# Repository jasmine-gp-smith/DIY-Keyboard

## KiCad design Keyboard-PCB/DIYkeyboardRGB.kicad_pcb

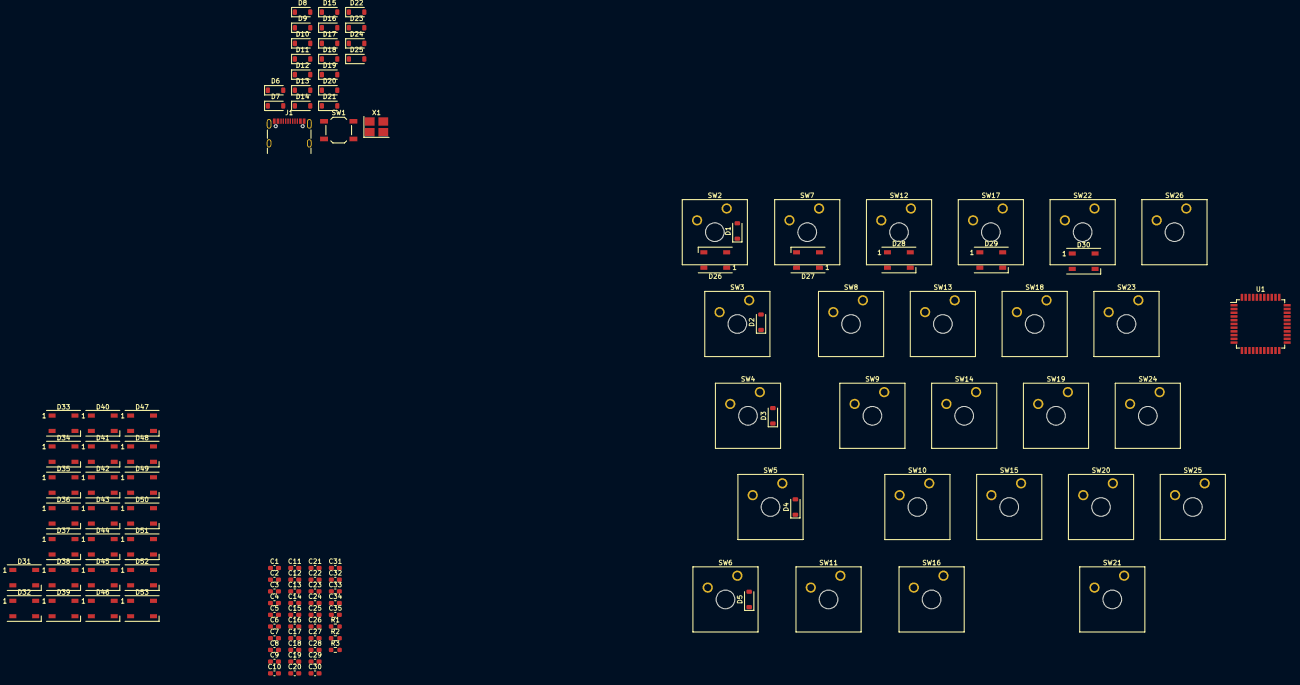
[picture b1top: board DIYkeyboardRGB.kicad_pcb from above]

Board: 2 copper layers, 120 parts (0 on the bottom side), 76 nets, no tracks yet.

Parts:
C1, C2, C3, C8, C9, C10, C11, C12, C13, C14, C15, C16, C17, C18, C19, C20, C21, C22, C23, C24, C25, C26, C27, C28, C29, C30, C31, C32, C33, C34, C35: 0.1u; C_0603_1608Metric_Pad1.08x0.95mm_HandSolder
C4: 4.yu; C_0603_1608Metric_Pad1.08x0.95mm_HandSolder
C5: 1u; C_0603_1608Metric_Pad1.08x0.95mm_HandSolder
C6, C7: 22p; C_0603_1608Metric_Pad1.08x0.95mm_HandSolder
D1, D2, D3, D4, D5, D6, D7, D8, D9, D10, D11, D12, D13, D14, D15, D16, D17, D18, D19, D20, D21, D22, D23, D24, D25: D; D_SOD-123
D26, D27, D28, D29, D30, D31, D32, D33, D34, D35, D36, D37, D38, D39, D40, D41, D42, D43, D44, D45, D46, D47, D48, D49, D50, D51, D52, D53: WS2812B; LED_WS2812B_PLCC4_5.0x5.0mm_P3.2mm
J1: USB_C_Receptacle_USB2.0; USB_C_Receptacle_GCT_USB4105-xx-A_16P_TopMnt_Horizontal
R1, R2: 10k; R_0603_1608Metric_Pad0.98x0.95mm_HandSolder
R3: 100; R_0603_1608Metric_Pad0.98x0.95mm_HandSolder
SW1: SW_Push; SW_SPST_TL3342
SW2, SW7, SW8, SW9, SW10, SW11, SW12, SW13, SW14, SW15, SW17, SW18, SW19, SW20, SW22, SW23, SW24, SW25, SW26: SW_DIP_x01; SW_Cherry_MX_1.00u_Plate
SW3: SW_DIP_x01; SW_Cherry_MX_1.50u_Plate
SW4: SW_DIP_x01; SW_Cherry_MX_1.75u_Plate
SW5: SW_DIP_x01; SW_Cherry_MX_2.25u_Plate
SW6, SW16: SW_DIP_x01; SW_Cherry_MX_1.25u_Plate
SW21: SW_DIP_x01; SW_Cherry_MX_2.75u_Plate
U1: ATmega32U4-A; TQFP-44_10x10mm_P0.8mm
X1: XTAL_GND; Crystal_SMD_3225-4Pin_3.2x2.5mm_HandSoldering

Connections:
+5V: C8.2, C9.2, C10.2, C11.2, C12.2, C13.2, C14.2, C15.2, C16.2, C17.2, C18.2, C19.2, C20.2, C21.2, C22.2, C23.2, C24.2, C25.2, C26.2, C27.2, C28.2, C29.2, C30.2, C31.2, C32.2, C33.2, C34.2, C35.2, D26.3 (VSS), D27.3 (VSS), D28.3 (VSS), D29.3 (VSS), D30.3 (VSS), D31.3 (VSS), D32.3 (VSS), D33.3 (VSS), D34.3 (VSS), D35.3 (VSS), D36.3 (VSS), D37.3 (VSS), D38.3 (VSS), D39.3 (VSS), D40.3 (VSS), D41.3 (VSS), D42.3 (VSS), D43.3 (VSS), D44.3 (VSS), D45.3 (VSS), D46.3 (VSS), D47.3 (VSS), D48.3 (VSS), D49.3 (VSS), D50.3 (VSS), D51.3 (VSS), D52.2 (DOUT), D52.3 (VSS), D53.3 (VSS)
D+: J1.A6 (D+), J1.B6 (D+), U1.4 (D+)
D-: J1.A7 (D-), J1.B7 (D-), U1.3 (D-)
LEDs: R3.1, U1.18 (PD0)
unnamed: D1.2 (A), SW2.1
unnamed: D2.2 (A), SW3.1
unnamed: D3.2 (A), SW4.1
unnamed: D4.2 (A), SW5.1
unnamed: D5.2 (A), SW6.1
unnamed: D6.2 (A), SW7.1
unnamed: D7.2 (A), SW8.1
unnamed: D8.2 (A), SW9.1
unnamed: D9.2 (A), SW10.1
unnamed: D10.2 (A), SW11.1
unnamed: D11.2 (A), SW12.1
unnamed: D12.2 (A), SW13.1
unnamed: D13.2 (A), SW14.1
unnamed: D14.2 (A), SW15.1
unnamed: D15.2 (A), SW16.1
unnamed: D16.2 (A), SW17.1
unnamed: D17.2 (A), SW18.1
unnamed: D18.2 (A), SW19.1
unnamed: D19.2 (A), SW20.1
unnamed: D20.2 (A), SW21.1
unnamed: D21.2 (A), SW22.1
unnamed: D22.2 (A), SW23.1
unnamed: D23.2 (A), SW24.1
unnamed: D24.2 (A), SW25.1
unnamed: D25.2 (A), SW26.1
unnamed: D26.4 (DIN), R3.2
unnamed: D26.2 (DOUT), D27.4 (DIN)
unnamed: D27.2 (DOUT), D28.4 (DIN)
unnamed: D28.2 (DOUT), D29.4 (DIN)
unnamed: D29.2 (DOUT), D30.4 (DIN)
unnamed: D30.2 (DOUT), D31.4 (DIN)
unnamed: D31.2 (DOUT), D32.4 (DIN)
unnamed: D32.2 (DOUT), D33.4 (DIN)
unnamed: D33.2 (DOUT), D34.4 (DIN)
unnamed: D34.2 (DOUT), D35.4 (DIN)
unnamed: D35.2 (DOUT), D36.4 (DIN)
unnamed: D36.2 (DOUT), D37.4 (DIN)
unnamed: D37.2 (DOUT), D38.4 (DIN)
unnamed: D38.2 (DOUT), D39.4 (DIN)
unnamed: D39.2 (DOUT), D40.4 (DIN)
unnamed: D40.2 (DOUT), D42.4 (DIN)
unnamed: D41.4 (DIN), D53.2 (DOUT)
unnamed: D41.2 (DOUT), D43.4 (DIN)
unnamed: D42.2 (DOUT), D45.4 (DIN)
unnamed: D43.2 (DOUT), D44.4 (DIN)
unnamed: D44.2 (DOUT), D46.4 (DIN)
unnamed: D45.2 (DOUT), D47.4 (DIN)
unnamed: D46.2 (DOUT), D48.4 (DIN)
unnamed: D47.2 (DOUT), D49.4 (DIN)
unnamed: D48.2 (DOUT), D50.4 (DIN)
unnamed: D49.2 (DOUT), D51.4 (DIN)
unnamed: D50.2 (DOUT), D52.4 (DIN)
unnamed: D51.2 (DOUT), D53.4 (DIN)
unnamed: C5.2, U1.6 (UCAP)
unnamed: R2.1, U1.33 (~HWB/PE2)
unnamed: R1.2, SW1.2, U1.13 (~RESET)
UCAP: C1.2, C2.2, C3.2, C4.2, C5.1, C6.2, C7.2, J1.A1 (GND), J1.A12 (GND), J1.B1 (GND), J1.B12 (GND), J1.S1 (SHIELD), R2.2, SW1.1, U1.5 (UGND), U1.15 (GND), U1.23 (GND), U1.35 (GND), U1.43 (GND), X1.3
VDD: C8.1, C9.1, C10.1, C11.1, C12.1, C13.1, C14.1, C15.1, C16.1, C17.1, C18.1, C19.1, C20.1, C21.1, C22.1, C23.1, C24.1, C25.1, C26.1, C27.1, C28.1, C29.1, C30.1, C31.1, C32.1, C33.1, C34.1, C35.1, D26.1 (VDD), D27.1 (VDD), D28.1 (VDD), D29.1 (VDD), D30.1 (VDD), D31.1 (VDD), D32.1 (VDD), D33.1 (VDD), D34.1 (VDD), D35.1 (VDD), D36.1 (VDD), D37.1 (VDD), D38.1 (VDD), D39.1 (VDD), D40.1 (VDD), D41.1 (VDD), D42.1 (VDD), D43.1 (VDD), D44.1 (VDD), D45.1 (VDD), D46.1 (VDD), D47.1 (VDD), D48.1 (VDD), D49.1 (VDD), D50.1 (VDD), D51.1 (VDD), D52.1 (VDD), D53.1 (VDD)
VUSB: C1.1, C2.1, C3.1, C4.1, J1.A4 (VBUS), J1.A9 (VBUS), J1.B4 (VBUS), J1.B9 (VBUS), R1.1, U1.2 (UVCC), U1.7 (VBUS), U1.14 (VCC), U1.24 (AVCC), U1.34 (VCC), U1.44 (AVCC)
col0: SW2.2, SW3.2, SW4.2, SW5.2, SW6.2, U1.36 (PF7)
col1: SW7.2, SW8.2, SW9.2, SW10.2, SW11.2, U1.37 (PF6)
col2: SW12.2, SW13.2, SW14.2, SW15.2, SW16.2, U1.38 (PF5)
col3: SW17.2, SW18.2, SW19.2, SW20.2, SW21.2, U1.39 (PF4)
col4: SW22.2, SW23.2, SW24.2, SW25.2, U1.40 (PF1)
col5: SW26.2, U1.41 (PF0)
row0: D1.1 (K), D6.1 (K), D11.1 (K), D16.1 (K), D21.1 (K), D25.1 (K), U1.8 (PB0)
row1: D2.1 (K), D7.1 (K), D12.1 (K), D17.1 (K), D22.1 (K), U1.9 (PB1)
row2: D3.1 (K), D8.1 (K), D13.1 (K), D18.1 (K), D23.1 (K), U1.10 (PB2)
row3: D4.1 (K), D9.1 (K), D14.1 (K), D19.1 (K), D24.1 (K), U1.11 (PB3)
row4: D5.1 (K), D10.1 (K), D15.1 (K), D20.1 (K), U1.28 (PB4)
xtal1: C6.1, U1.17 (XTAL1), X1.1
xtal2: C7.1, U1.16 (XTAL2), X1.2

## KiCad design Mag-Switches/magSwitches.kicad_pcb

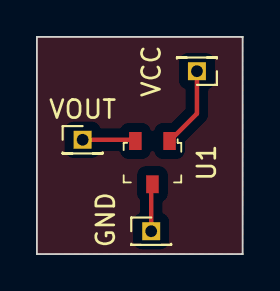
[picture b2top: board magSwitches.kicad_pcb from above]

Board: 2 copper layers, 11.4 x 12.1 mm, 4 parts (0 on the bottom side), 3 nets.

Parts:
GND: Conn_01x01_Pin; PinHeader_1x01_P1.27mm_Vertical
U1: A1324LLHLT-T; SOT-23W
VCC: Conn_01x01_Pin; PinHeader_1x01_P1.27mm_Vertical
VOUT: Conn_01x01_Pin; PinHeader_1x01_P1.27mm_Vertical

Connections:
unnamed: U1.2 (VOUT), VOUT.1
unnamed: U1.1 (VCC), VCC.1
unnamed: GND.1, U1.3 (GND)

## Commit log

2023-10-18 Create Keyboard-PCB
2023-10-18 Delete Keyboard-PCB
    testing things out
2023-10-18 Delete Mag-Switches/.placeholder
    test
2023-10-18 Add files via upload
    Schematic for normal switches
    TODO: Modify for mag switches, connect to ADC pins, change switch footprint (if necessary), try to add hot-swap sockets
